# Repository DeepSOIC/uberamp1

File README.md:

# Feautures

* output channels: 8 independent(*) single-ended power outputs (TPA3255) + 2 headphone-amplified output channels + 2 non-amplified adau1701 dacs
    * independent 8 single-ended outputs can be arbitrarily combined into btl or even 3-phase-like arrangements.
    * BTL protections of the tpa chip can be enabled with solder bridges on the board
    * headphone amplifier output 9 Vpp.
* two tpa3255 amps, with power up to 54 V and output current trip at 17 A per channel (**)
* easy-to-program yet flexible adau1701 dsp chip, with self-boot memory on the board
* low-noise AK4454 dacs
* SNR 111 dB in BTL and 101 db in SE (theoretical, unverified so far).
* 2 "feedbass" amplifiers on board, and places for resistors for custom analog mixing of feedbass into outputs.
* capacitor-free (***) analog signal path (except analog inputs) allows to output dc, so uberamp1 can be used to drive motors
* 2 analog input channels (2.5Vpp) (AC-coupled ground-referenced; DC coupling possible with an addon board)
* bluetooth receiver with digital connection to the dsp (firmware = TODO)
* pads for summing inputs for each amp channel to allow adding custom analog feedbacks
* fan control circuit

(*) there is no place for decoupling capacitors on the board. So you might use one of the outputs as "ground", leaving you with 7 channels. In BTL, there are 4 output channels.

(**) not fully tested yet. At high supply voltage or high load currents, heatsinking becomes a challenge. It dissipates about 11W total in silence at 48 V. It was really not designed to push out the full power continuously, it was designed so to handle transients well.

(***) there are footprints for dc blocking caps. Install jumpers if DC coupling is desired.

# known problems (v1.1):

* power amps don't start exactly in sync, causing large excursion at powerup if a speaker is connected between amps (it does so quietly, so it's not too bad). Seems unfixable.
* it is challenging to solder.
* i was unable to program the bluetooth chip to work with this amplifier so far.
* a fan is required at 48V supply voltage. It can work fanless if only one amplifier chip is active, or if the supply voltage is lower. 

# soldering 

Manufacturability is still slightly screwed up on v1.1.

While the board was designed for hand-soldering, but it also works with reflow soldering.
But footprints for 10uf bypass caps are now a little too large, they are prone to shifts to one pad during reflow.
And the rows of resistors next to dacs are placed too dense, and are prone to shorting together.

Top side can be reflow-soldered. 
Bottom side must be done by hand.

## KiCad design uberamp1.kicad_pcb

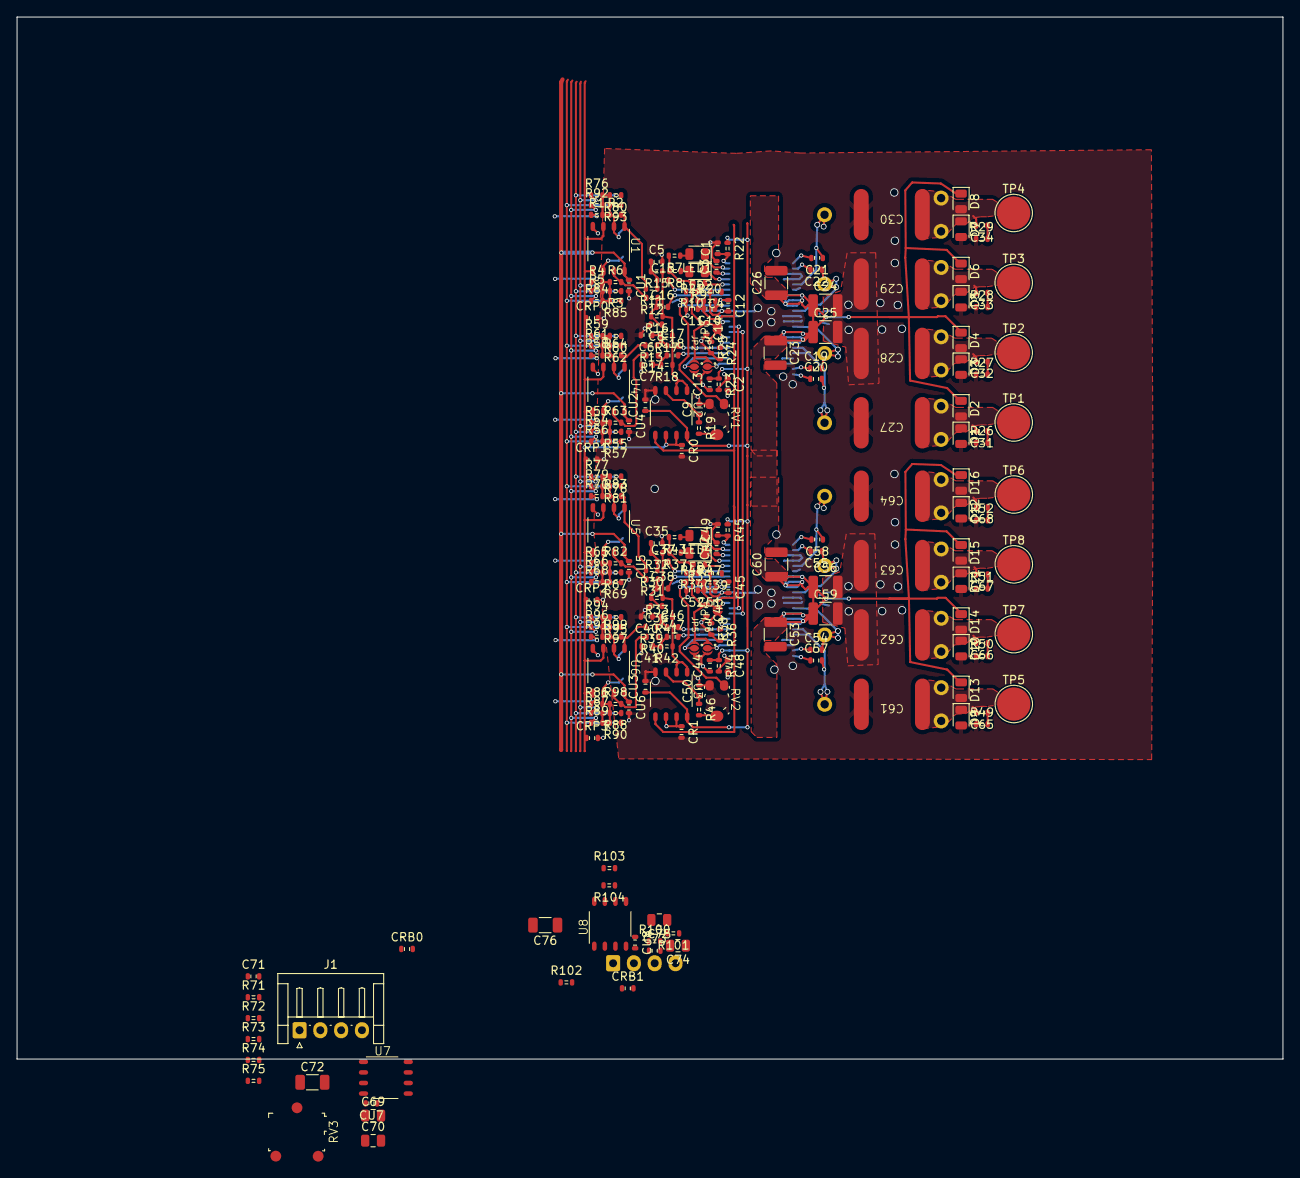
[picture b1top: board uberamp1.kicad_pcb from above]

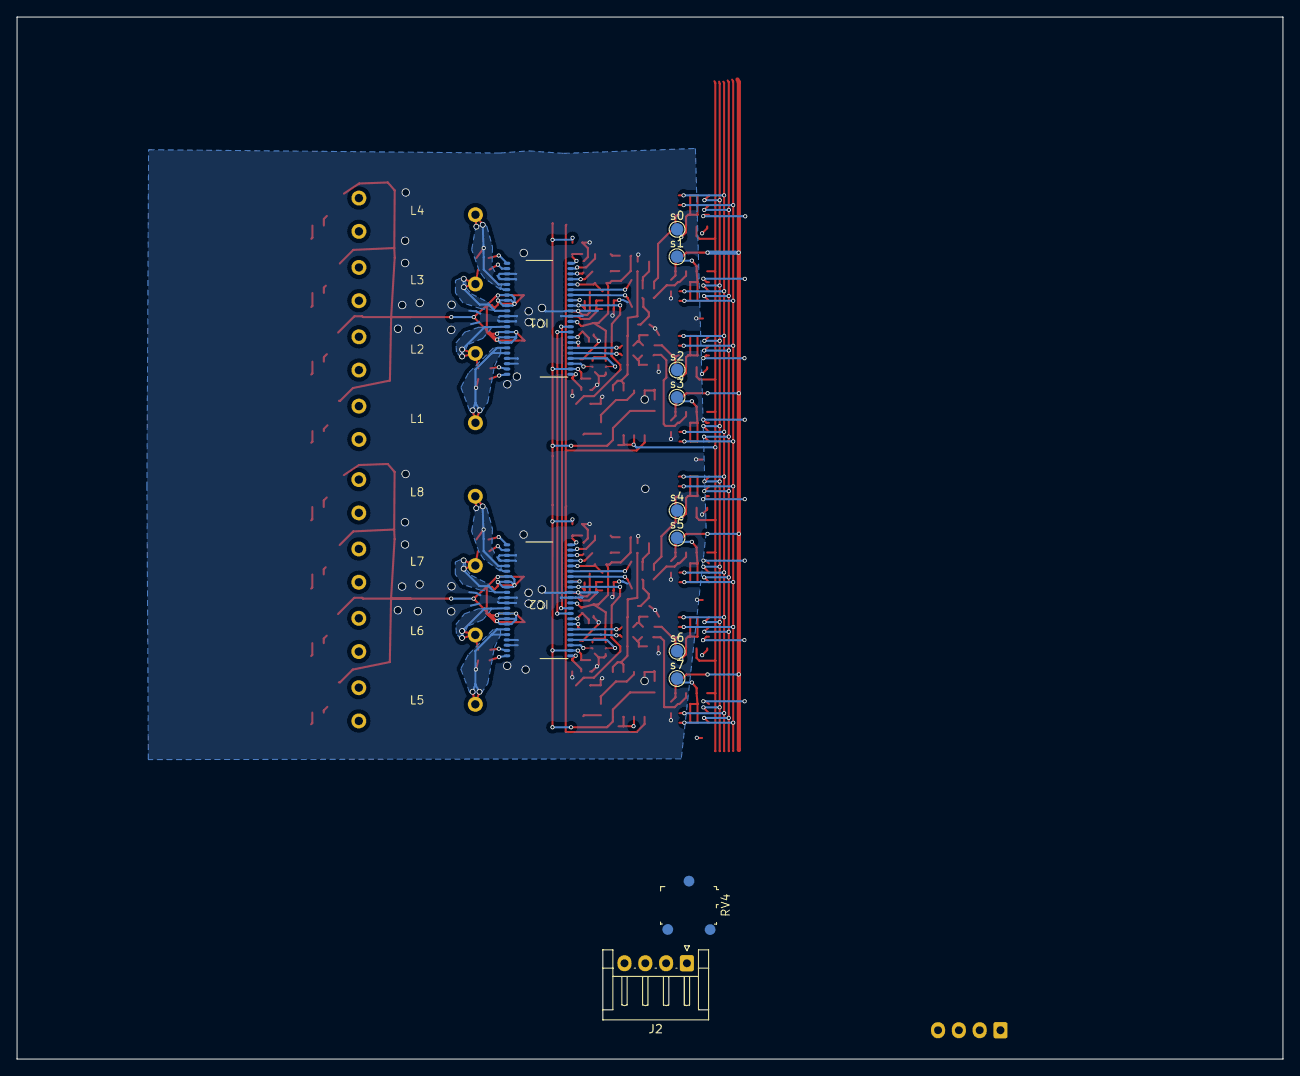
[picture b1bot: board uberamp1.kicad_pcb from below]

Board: 2 copper layers, 152.1 x 125.2 mm, 262 parts (20 on the bottom side), 124 nets.

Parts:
C1, C2, C13, C15, C16, C17, C18, C37, C38, C44, C46, C47, C48, C49: 10u; C_0603
C3, C9, C12, C42, C45, C50: 1u; C_0603
C4, C39: 100p; C_0603
C5, C6, C7, C8, C35, C36, C40, C41: 4.7n; C_0603
C10, C11, C51, C52: 2.2u; C_0603
C14, C43: 1uF; C_0603
C19, C20, C21, C22, C54, C55, C57, C58: 33n; C_0603
C23, C24, C25, C26, C53, C56, C59, C60: 10u 63V; C_1210_3225Metric
C27, C28, C29, C30, C61, C62, C63, C64: 1uF 63V; CB052D0105KBC film cap
C31, C32, C33, C34, C65, C66, C67, C68: 10nF; C_0603
C69, C74: tbd; C_0805_2012Metric
C70, C75: 1nF; C_0805_2012Metric
C71, C73: 100nF; C_0603
C72, C76: 0.33uF; C_1206_3216Metric
CR0, CR1: 10u; C_0603
CRB0, CRB1: 10u; C_0603
CRP0, CRP1, CRP2, CRP3: 10u; C_0603
CU1, CU2, CU3, CU4, CU5, CU6, CU7, CU8: 10u; C_0603
D1, D2, D3, D4, D5, D6, D7, D8, D9, D10, D11, D12, D13, D14, D15, D16: D_Schottky; D_0805_2012Metric
IC1, IC2: TPA3255; tssop44-powerpad
J1, J2: Conn_01x04; JST_EH_S4B-EH_1x04_P2.50mm_Horizontal
JP1, JP2, JP5, JP6: SolderJumper_3_Bridged12; solder-switch
JP3, JP4: slave; solder-jumper
L1, L2, L3, L4, L5, L6, L7, L8: 10uH 14A; SPM12565VT-D-vertical
LED1, LED4: clipping; LED_0805_2012Metric
LED2, LED3: fault; LED_0805_2012Metric
R1, R4, R53, R58, R65, R70, R86, R91: R_Small; R_0603
R2, R6, R63, R64, R71, R72, R82, R83, R98, R99, R103, R104: 2k; R_0603
R3, R5, R54, R55, R56, R57, R59, R60, R61, R62, R66, R67, R68, R69, R76, R77, R78, R79, R80, R81, R84, R85, R87, R88, R89, R90, R92, R93, R94, R95, R96, R97: 3.6k; R_0603
R7, R8, R37, R43: 2.7K; R_0603
R9, R19, R35, R46: 47k; R_0603
R10, R34, R75, R100: 100; R_0603
R11, R12, R13, R14, R30, R31, R39, R40: 330; R_0603
R15, R16, R17, R18, R32, R33, R41, R42: 10k; R_0603
R20, R21, R47, R48: 4.7k; R_0603
R22, R23, R26, R27, R28, R29, R44, R45, R49, R50, R51, R52: 3.3; R_0603
R24, R36: 27k; R_0603
R25, R38, R73, R101: 30k; R_0603
R74, R102: 240; R_0603
RV1, RV2: 10k; TC33X-2 trimpot
RV3, RV4: 1k; PV37X
TP1, TP5: out3; TestPoint_Pad_D4.0mm
TP2, TP7: out2; TestPoint_Pad_D4.0mm
TP3, TP8: out1; TestPoint_Pad_D4.0mm
TP4, TP6: out0; TestPoint_Pad_D4.0mm
U1, U2, U3, U4, U5, U6, U7, U8: Opamp_Dual; SOIC-8
s0, s1, s2, s3, s4, s5, s6, s7: sum0; TestPoint_Pad_D1.5mm

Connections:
/12V: C13.2, C44.2, CU1.1, CU2.1, CU3.1, CU4.1, CU5.1, CU6.1, CU7.1, CU8.1, IC1.2 (2_VDD), IC2.2 (2_VDD), R22.1, R23.1, R44.1, R45.1, U1.8 (V+), U2.8 (V+), U3.8 (V+), U4.8 (V+), U5.8 (V+), U6.8 (V+), U7.8 (V+), U8.8 (V+)
/fb0: C72.1, R5.1, R54.1, R59.1, R66.1, R71.1, R74.2, R76.1, R77.1, R87.1, R94.1
/fb1: C76.1, R56.1, R61.1, R68.1, R79.1, R84.1, R89.1, R92.1, R96.1, R102.2, R103.1
/inputref: C69.2, C70.2, C72.2, C74.2, C75.2, C76.2, CR0.1, CRB0.1, CRB1.1, CRP0.1, CRP1.1, CRP2.1, CRP3.1, R75.2, R100.2, RV3.3, RV4.3, U1.3 (+), U1.5 (+), U2.6 (-), U2.7, U4.3 (+), U4.5 (+), U5.3 (+), U5.5 (+), U6.3 (+), U6.5 (+), U7.5 (+), U8.5 (+)
/poweramp1/AVDD: C51.1, IC2.14 (14_AVDD), R47.2, RV2.3
/poweramp1/DVDD: C43.1, IC2.11 (11_DVDD), JP4.2 (B), JP5.1 (A), JP6.1 (A), R35.2, R37.2, R43.2
/poweramp1/in0: R30.2, R83.2, U5.1
/poweramp1/in1: R31.2, R82.2, U5.7
/poweramp1/in2: R39.2, R99.2, U6.1
/poweramp1/in3: R40.2, R98.2, U6.7
/poweramp1/in_a: C47.2, IC2.5 (5_INPUT_A)
/poweramp1/in_b: C46.2, IC2.6 (6_INPUT_B)
/poweramp1/in_c: C38.2, IC2.16 (16_INPUT_C)
/poweramp1/in_d: C37.2, IC2.17 (17_INPUT_D)
/poweramp1/input_ref: CR1.1, U3.6 (-), U3.7
/poweramp1/out0: C64.1, C68.2, D12.1 (K), D16.2 (A), L8.1, TP6.1
/poweramp1/out1: C63.1, C67.2, D11.1 (K), D15.2 (A), L7.1, TP8.1
/poweramp1/out2: C62.1, C66.2, D10.1 (K), D14.2 (A), L6.1, TP7.1
/poweramp1/out3: C61.1, C65.2, D9.1 (K), D13.2 (A), L5.1, TP5.1
/poweramp1/sw0: C58.1, IC2.27 (27_OUT_D), IC2.28 (28_OUT_D____________), L8.2
/poweramp1/sw1: C55.1, IC2.32 (32_OUT_C), L7.2
/poweramp1/sw2: C54.2, IC2.35 (35_OUT_B), L6.2
/poweramp1/sw3: C57.2, IC2.39 (39_OUT_A), IC2.40 (40_OUT_A____________), L5.2
/poweramp1/trim: R32.1, R33.1, R41.1, R42.1, U3.1, U3.2 (-)
/poweramp/AVDD: C10.1, IC1.14 (14_AVDD), R20.2, RV1.3
/poweramp/DVDD: C14.1, IC1.11 (11_DVDD), JP1.1 (A), JP2.1 (A), JP3.2 (B), R7.2, R8.2, R9.2
/poweramp/in0: R2.2, R11.2, U1.1
/poweramp/in1: R6.2, R12.2, U1.7
/poweramp/in2: R13.2, R64.2, U4.1
/poweramp/in3: R14.2, R63.2, U4.7
/poweramp/in_a: C18.2, IC1.5 (5_INPUT_A)
/poweramp/in_b: C17.2, IC1.6 (6_INPUT_B)
/poweramp/in_c: C16.2, IC1.16 (16_INPUT_C)
/poweramp/in_d: C15.2, IC1.17 (17_INPUT_D)
/poweramp/input_ref_z: C10.2, C11.1, C51.2, C52.1, R20.1, R21.2, R47.1, R48.2, U2.5 (+), U3.5 (+)
/poweramp/osc+: IC1.10 (10_OSC_IOP), IC2.10 (10_OSC_IOP)
/poweramp/osc-: IC1.9 (9_OSC_IOM), IC2.9 (9_OSC_IOM)
/poweramp/out0: C30.1, C34.2, D7.1 (K), D8.2 (A), L4.1, TP4.1
/poweramp/out1: C29.1, C33.2, D5.1 (K), D6.2 (A), L3.1, TP3.1
/poweramp/out2: C28.1, C32.2, D3.1 (K), D4.2 (A), L2.1, TP2.1
/poweramp/out3: C27.1, C31.2, D1.1 (K), D2.2 (A), L1.1, TP1.1
/poweramp/sw0: C21.1, IC1.27 (27_OUT_D), IC1.28 (28_OUT_D____________), L4.2
/poweramp/sw1: C22.1, IC1.32 (32_OUT_C), L3.2
/poweramp/sw2: C19.2, IC1.35 (35_OUT_B), L2.2
/poweramp/sw3: C20.2, IC1.39 (39_OUT_A), IC1.40 (40_OUT_A____________), L1.2
/poweramp/trim: R15.1, R16.1, R17.1, R18.1, U2.1, U2.2 (-)
/~fb0: R3.1, R55.1, R60.1, R67.1, R72.2, R78.1, R80.1, R88.1, R95.1, U7.7
/~fb1: R57.1, R62.1, R69.1, R81.1, R85.1, R90.1, R93.1, R97.1, R104.2, U8.7
GND: C1.2, C2.2, C3.2, C4.2, C5.2, C6.2, C7.2, C8.2, C9.2, C11.2, C12.2, C13.1, C14.2, C23.2, C24.2, C25.2, C26.2, C27.2, C28.2, C29.2, C30.2, C35.2, C36.2, C39.2, C40.2, C41.2, C42.2, C43.2, C44.1, C45.2, C48.2, C49.2, C50.2, C52.2, C53.2, C56.2, C59.2, C60.2, C61.2, C62.2, C63.2, C64.2, C71.2, C73.2, CR0.2, CR1.2, CRB0.2, CRB1.2, CRP0.2, CRP1.2, CRP2.2, CRP3.2, CU1.2, CU2.2, CU3.2, CU4.2, CU5.2, CU6.2, CU7.2, CU8.2, D1.2 (A), D3.2 (A), D5.2 (A), D7.2 (A), D9.2 (A), D10.2 (A), D11.2 (A), D12.2 (A), IC1.12 (12_GND), IC1.13 (13_GND), IC1.25 (25_GND), IC1.26 (26_GND), IC1.33 (33_GND), IC1.34 (34_GND), IC1.41 (41_GND), IC1.42 (42_GND), IC2.12 (12_GND), IC2.13 (13_GND), IC2.25 (25_GND), IC2.26 (26_GND), IC2.33 (33_GND), IC2.34 (34_GND), IC2.41 (41_GND), IC2.42 (42_GND), JP1.3 (B), JP2.3 (B), JP5.3 (B), JP6.3 (B), R21.1, R24.2, R25.2, R26.1, R27.1, R28.1, R29.1, R36.2, R38.2, R48.1, R49.1, R50.1, R51.1, R52.1, RV1.1, RV2.1, U1.4 (V-), U2.4 (V-), U3.4 (V-), U4.4 (V-), U5.4 (V-), U6.4 (V-), U7.4 (V-), U8.4 (V-)
unnamed: C5.1, C15.1, R11.1, R15.2
unnamed: C8.1, C16.1, R12.1, R16.2
unnamed: C6.1, C17.1, R13.1, R17.2
unnamed: C7.1, C18.1, R14.1, R18.2
unnamed: C31.1, R26.2
unnamed: C32.1, R27.2
unnamed: C33.1, R28.2
unnamed: C34.1, R29.2
unnamed: C35.1, C37.1, R30.1, R32.2
unnamed: C36.1, C38.1, R31.1, R33.2
unnamed: C40.1, C46.1, R39.1, R41.2
unnamed: C41.1, C47.1, R40.1, R42.2
unnamed: C65.1, R49.2
unnamed: C66.1, R50.2
unnamed: C67.1, R51.2
unnamed: C68.1, R52.2
unnamed: C2.1, IC1.1 (1_GVDD_AB), R23.2
unnamed: IC1.3 (3_M1), JP1.2 (C)
unnamed: IC1.4 (4_M2), JP2.2 (C)
unnamed: IC1.7 (7_OC_ADJ), R24.1
unnamed: IC1.8 (8_FREQ_ADG), JP3.1 (A), R25.1
unnamed: C12.1, IC1.15 (15_C_START)
unnamed: C4.1, IC1.18 (18_RESET), R9.1, R10.1
unnamed: IC1.19 (19_FAULT), LED2.1 (K)
unnamed: C3.1, IC1.20 (20_VBG)
unnamed: IC1.21 (21_CLIP_OTW), LED1.1 (K)
unnamed: C1.1, IC1.22 (22GVDD_CD), R22.2
unnamed: C21.2, IC1.23 (23_BST_D)
unnamed: C22.2, IC1.24 (24_BST_C)
unnamed: C19.1, IC1.43 (43_BST_B)
unnamed: C20.1, IC1.44 (44_BST_A)
unnamed: C48.1, IC2.1 (1_GVDD_AB), R44.2
unnamed: IC2.3 (3_M1), JP6.2 (C)
unnamed: IC2.4 (4_M2), JP5.2 (C)
unnamed: IC2.7 (7_OC_ADJ), R36.1
unnamed: IC2.8 (8_FREQ_ADG), JP4.1 (A), R38.1
unnamed: C45.1, IC2.15 (15_C_START)
unnamed: C39.1, IC2.18 (18_RESET), R34.1, R35.1
unnamed: IC2.19 (19_FAULT), LED3.1 (K)
unnamed: C42.1, IC2.20 (20_VBG)
unnamed: IC2.21 (21_CLIP_OTW), LED4.1 (K)
unnamed: C49.1, IC2.22 (22GVDD_CD), R45.2
unnamed: C58.2, IC2.23 (23_BST_D)
unnamed: C55.2, IC2.24 (24_BST_C)
unnamed: C54.1, IC2.43 (43_BST_B)
unnamed: C57.1, IC2.44 (44_BST_A)
unnamed: C71.1, J1.3, R75.1
unnamed: C69.1, J1.4, R73.1
unnamed: C73.1, J2.3, R100.1
unnamed: C74.1, J2.4, R101.1
unnamed: LED1.2 (A), R7.1
unnamed: LED2.2 (A), R8.1
unnamed: LED3.2 (A), R37.1
unnamed: LED4.2 (A), R43.1
unnamed: R19.2, RV1.2
unnamed: R46.2, RV2.2
unnamed: R74.1, RV3.1, U7.1
unnamed: R102.1, RV4.1, U8.1
unnamed: R1.2, R2.1, R76.2, R80.2, R92.2, R93.2, U1.2 (-), s0.1
unnamed: R3.2, R4.2, R5.2, R6.1, R84.2, R85.2, U1.6 (-), s1.1
unnamed: C9.1, R19.1, U2.3 (+)
unnamed: C50.1, R46.1, U3.3 (+)
unnamed: R58.2, R59.2, R60.2, R61.2, R62.2, R64.1, U4.2 (-), s2.1
unnamed: R53.2, R54.2, R55.2, R56.2, R57.2, R63.1, U4.6 (-), s3.1
unnamed: R70.2, R77.2, R78.2, R79.2, R81.2, R83.1, U5.2 (-), s4.1
unnamed: R65.2, R66.2, R67.2, R68.2, R69.2, R82.1, U5.6 (-), s5.1
unnamed: R91.2, R94.2, R95.2, R96.2, R97.2, R99.1, U6.2 (-), s6.1
unnamed: R86.2, R87.2, R88.2, R89.2, R90.2, R98.1, U6.6 (-), s7.1
unnamed: C70.1, R73.2, U7.3 (+)
unnamed: RV3.2, U7.2 (-)
unnamed: R71.2, R72.1, U7.6 (-)
unnamed: C75.1, R101.2, U8.3 (+)
unnamed: RV4.2, U8.2 (-)
unnamed: R103.2, R104.1, U8.6 (-)
PVDD: C23.1, C24.1, C25.1, C26.1, C53.1, C56.1, C59.1, C60.1, D2.1 (K), D4.1 (K), D6.1 (K), D8.1 (K), D13.1 (K), D14.1 (K), D15.1 (K), D16.1 (K), IC1.29 (29_PVDD_CD), IC1.30 (30_PVDD_CD), IC1.31 (31_PVDD_CD), IC1.36 (36_PVDD_AB), IC1.37 (37_PVDD_AB), IC1.38 (38_PVDD_AB), IC2.29 (29_PVDD_CD), IC2.30 (30_PVDD_CD), IC2.31 (31_PVDD_CD), IC2.36 (36_PVDD_AB), IC2.37 (37_PVDD_AB), IC2.38 (38_PVDD_AB)

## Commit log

2024-02-18 about to breaking change
    state of things prior to switching poweramp instances in schematic
2024-02-18 add bypass caps to opamps + swap poweramps + layout progress
2024-02-18 route 1 preamp
2024-02-18 add replicate_layout.log to gitignore
2024-02-18 route all preamps
2024-02-18 add bypass caps to fakegnd
2024-02-18 update feedbass components
2024-02-18 fix feedbass filter
2024-02-29 add dacs to schematic
2024-03-03 minor schematic updates
2024-03-03 add step-down regulators to schematic
2024-03-04 tweak supplies schematic
2024-03-04 add clock source to schematic
2024-06-20 add dsp and esp32... schematic mostly done
2024-06-21 update to kicad 8
2024-06-23 schematic: some fixes
2024-06-23 updates
    * add line out
    * fix almost all erc
    * some more random edits
2024-06-30 add power input +...
    + tons of fixes, footprint assignments, etc
2024-07-02 some routing till got stuck
    got stuck on U16's power part somehow being on a different sheet
2024-07-02 fix gate association U15 U16
2024-07-02 routing...
    + swap around dac channels, otherwise routing was crazy
2024-07-02 more routing...
2024-07-04 routing routing...
2024-07-06 lots of drc-related work
2024-07-06 update some footprints
2024-07-06 silkscreen works + fixes
2024-07-06 more silkscreen
2024-07-06 fixes
2024-07-06 tweaks
    round size
    add some new pads
2024-07-06 board outline
    + fix voltage range label
2024-07-07 final touches. Sent for production.
2024-07-07 margin cut test (no effect)
2024-07-08 fix board edge clearance
2024-07-08 fill in some part numbers
2024-07-12 bom config
2024-07-12 update partnumbers to what was bought
2024-07-12 print cheatsheets
2024-07-19 add summation resistor layout cheatsheet
2024-07-19 workaround major gain/signal margin error
    using the components i have at hand. There probably are better options. Next revision should make use of the -5v rail.
2024-07-29 update values to what's being used + mark thin film resistors
2024-08-02 add more bugs
2024-08-02 work on bugs...
2024-08-11 begin specs
2024-08-11 work on bugs
    * align parts
    * enlarge cercaps
    * fix ak caps
    * improve jack footprint
    * fix lmr stencil openings
    * remove one ldo
2024-08-11 remove duplicate dac supply
2024-08-14 layout edits
2024-08-14 add fan control circuit
2024-08-14 remove ground around thermistor
2024-08-17 add esp-related bugs
2024-08-18 add cap for esp autoreset
2024-08-20 reroute feedbass amps
    + add the missing discharge resistor
2024-08-20 Update bugs v1.txt
    update bugs
2024-08-22 work on bugs
2024-08-24 all known bugs fixed
2024-09-02 touch-up
2024-09-02 fab v1.1
2024-09-09 rename testpoints?
    i don't think it was intentional...
2024-09-09 design pasting plate
2024-09-10 fix pasting plate
    board thickness error
2024-09-11 updates for better bom
2024-09-11 pcb prepare for cheatsheet
2024-09-11 cheatsheet fixup
2024-09-11 update cheatsheet
2024-09-11 preparations for bom
2024-09-11 more bom updates
2024-10-15 update boms
2024-10-15 update bugs
2024-11-20 fix connector part number
2024-11-20 full bom
    with assembly variants
